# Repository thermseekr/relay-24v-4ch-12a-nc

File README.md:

# eumesmo-rl-4ch12a-nc

Relay board with 4x 24 VDC NC relays. This board is designed to be used togheter with [eumesmo-io-24v16ch](https://github.com/thermseekr/eumesmo-io-24v16ch), but can be driven by any 24V control circuit compatible with NPN inputs. It uses Omron 16A relays and is limited to 12A/channel per copper trace capacity.

The board is compatible with the SP7 DIN rail system from Metaltex.

## VERSION HISTORY

V1.2 - 2026/06/13 - Repository renamed from RELAY-24V-4CH-12A-NC to eumesmo-rl-4ch12A-nc to align the design with the eumesmo line of building automation products.

V1.1 - 2026/06/13 - Input terminal blocks replaced from 2.54mm to 3.5mm pitch for easier installation in the field.

V1.0 - Initial release.

## LICENSE

This project is licensed under the [Creative Commons BY-NC 4.0 License](https://creativecommons.org/licenses/by-nc/4.0/).
Commercial use is not permitted without prior written consent. See the [LICENSE.txt](LICENSE.txt) file for details.

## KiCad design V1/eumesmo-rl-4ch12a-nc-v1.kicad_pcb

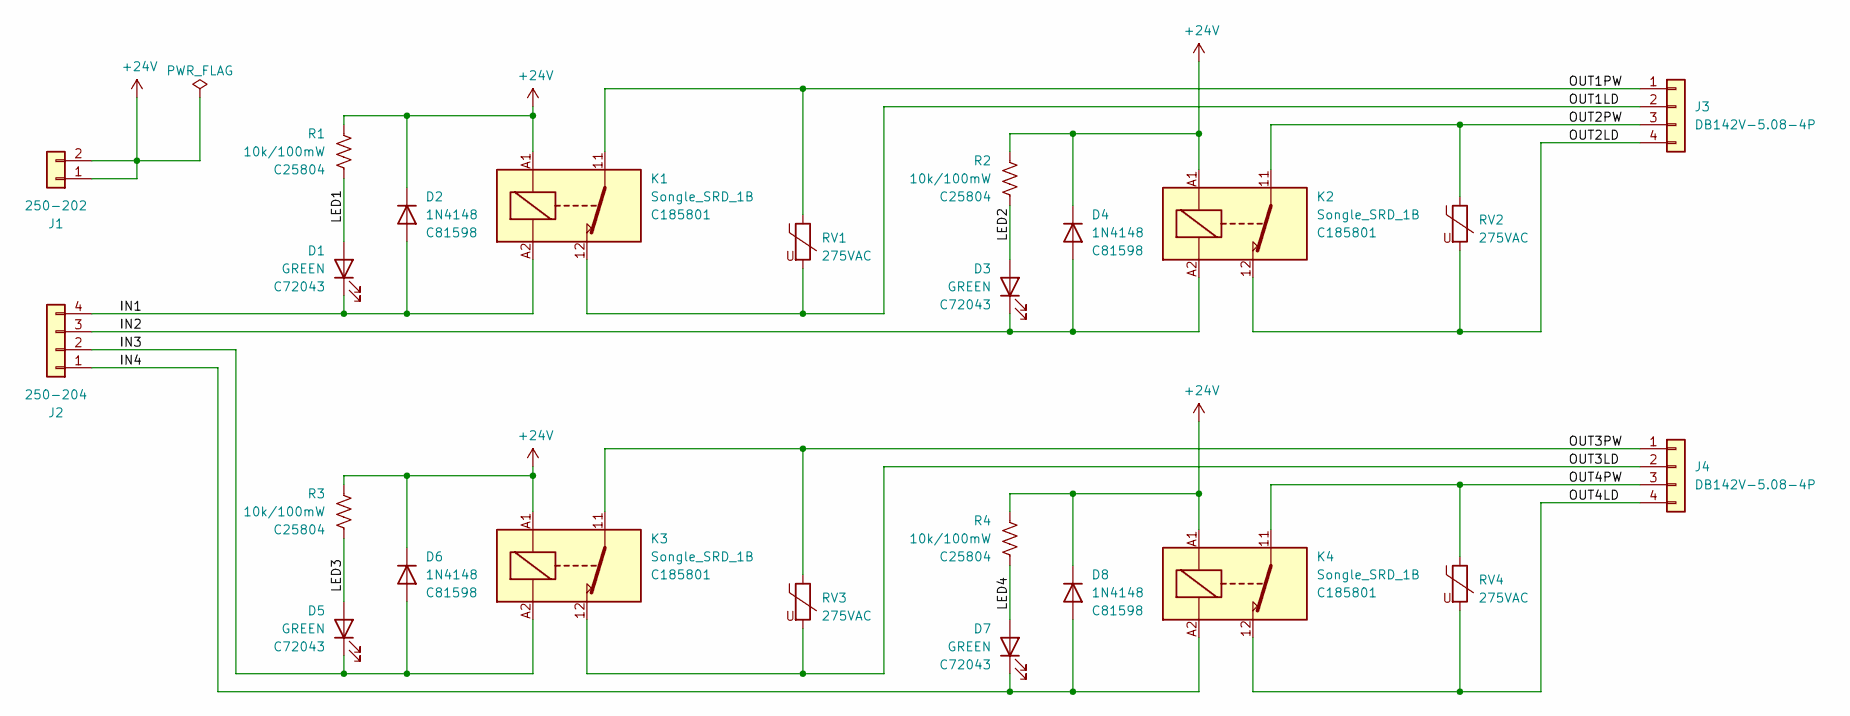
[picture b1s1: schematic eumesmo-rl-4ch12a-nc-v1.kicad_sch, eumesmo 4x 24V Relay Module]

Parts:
D1, D3, D5, D7: GREEN; LED_0603_1608Metric; Mfr PN 19-217/GHC-YR1S2/3T; LCSC Part # C72043
D2, D4, D6, D8: 1N4148; D_SOD-123; Mfr PN 1N4148W; LCSC Part # C81598
J1: 250-202; TerminalBlock_Wago_250-202_1x02_P3.5mm_45Degree; Mfr PN 250-202; JLCPCB BOM 1
J2: 250-204; TerminalBlock_Wago_250-204_1x04_P3.5mm_45Degree; Mfr PN 250-204; JLCPCB BOM 1
J3, J4: DB142V-5.08-4P; TerminalBlock_Dibo_DB142V-5.08-4P_1x04_P5.08mm_Vertical; Mfr PN DB142V-5.08-4P-GN; JLCPCB BOM 1
K1, K2, K3, K4: Songle_SRD_1B; Relay_SPST_Songle_SRD_FormB; Mfr PN SRD-24VDC-SL-B; JLCPCB BOM 1
R1, R2, R3, R4: 10k/100mW; R_0603_1608Metric; Mfr PN 0603WAF1002T5E; LCSC Part # C25804
RV1, RV2, RV3, RV4: 275VAC; RV_Disc_D9.50mm_W3.6mm_P5.08mm; Mfr PN RM07D431KC1IE100; JLCPCB BOM 1

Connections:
+24V: D2.1 (K), D4.1 (K), D6.1 (K), D8.1 (K), J1.1, J1.2, K1.A1, K2.A1, K3.A1, K4.A1, R1.1, R2.1, R3.1, R4.1
/IN1: D1.1 (K), D2.2 (A), J2.4, K1.A2
/IN2: D3.1 (K), D4.2 (A), J2.3, K2.A2
/IN3: D5.1 (K), D6.2 (A), J2.2, K3.A2
/IN4: D7.1 (K), D8.2 (A), J2.1, K4.A2
/LED1: D1.2 (A), R1.2
/LED2: D3.2 (A), R2.2
/LED3: D5.2 (A), R3.2
/LED4: D7.2 (A), R4.2
/OUT1LD: J3.2, K1.12, RV1.2
/OUT1PW: J3.1, K1.11, RV1.1
/OUT2LD: J3.4, K2.12, RV2.2
/OUT2PW: J3.3, K2.11, RV2.1
/OUT3LD: J4.2, K3.12, RV3.2
/OUT3PW: J4.1, K3.11, RV3.1
/OUT4LD: J4.4, K4.12, RV4.2
/OUT4PW: J4.3, K4.11, RV4.1

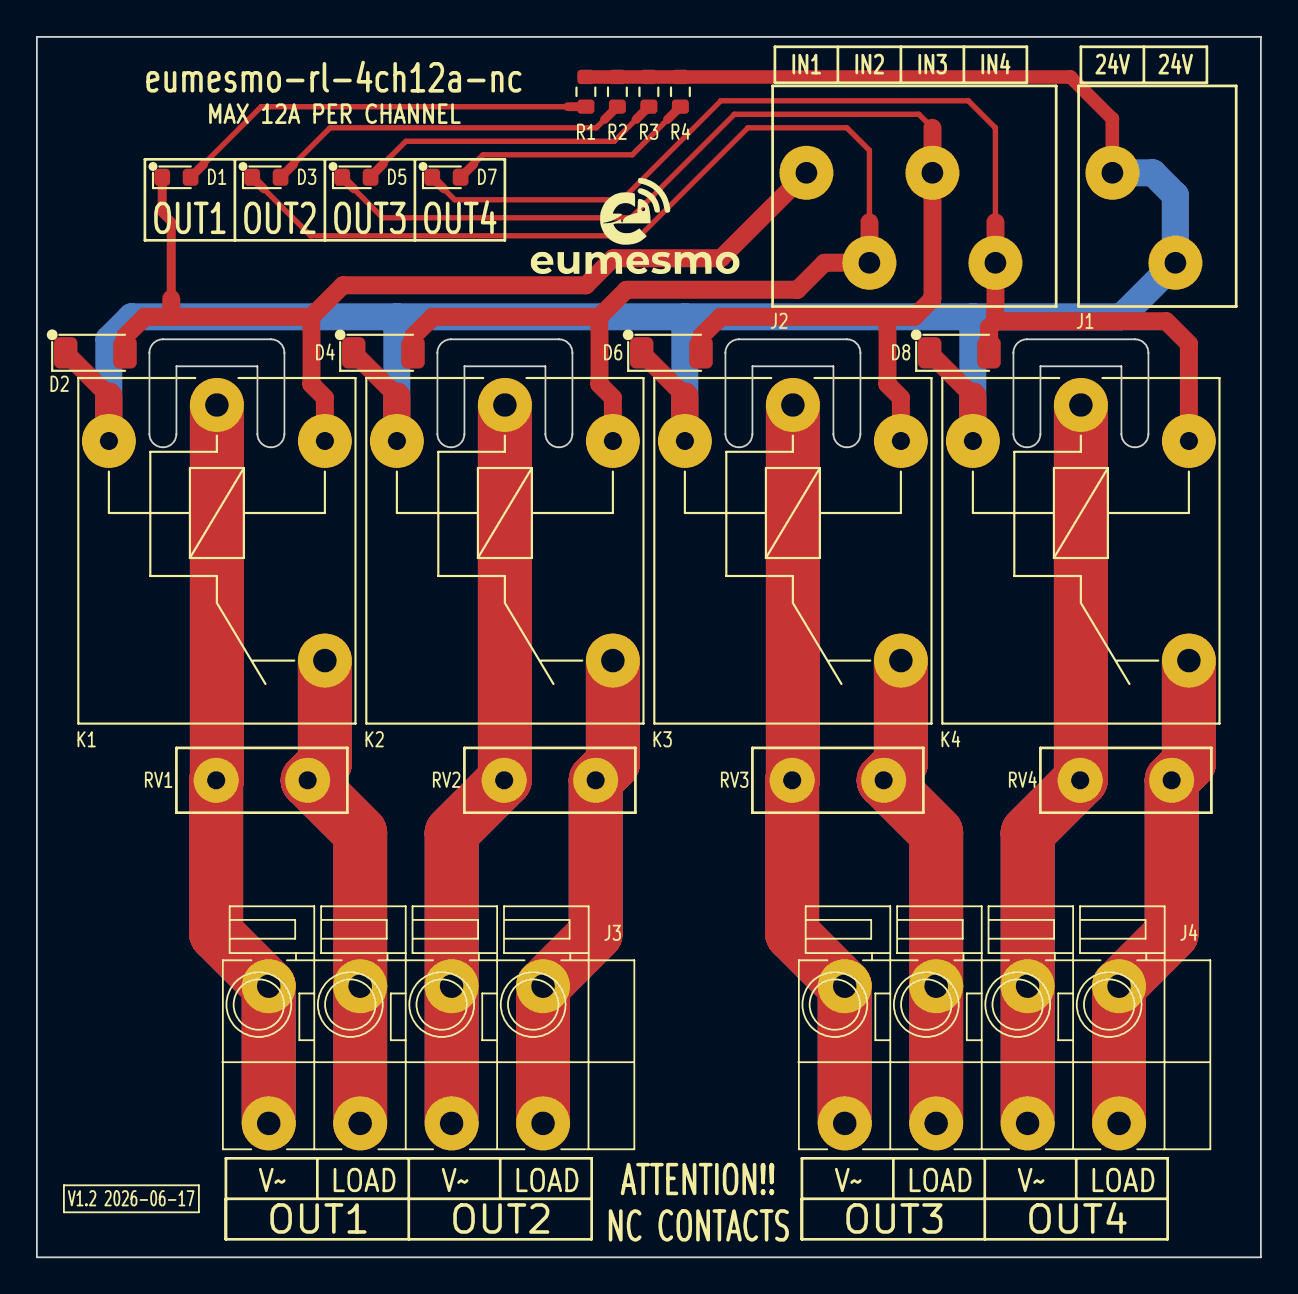
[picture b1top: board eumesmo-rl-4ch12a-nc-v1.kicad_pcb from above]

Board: 2 copper layers, 68.0 x 67.8 mm, 24 parts (0 on the bottom side), 17 nets.

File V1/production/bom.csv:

Designator,Footprint,Quantity,Value,LCSC Part #
"D1, D3, D5, D7",0603,4,GREEN,C72043
"D2, D4, D6, D8",D_SOD-123,4,1N4148,C81598
J1,TerminalBlock_Wago_250-202_1x02_P3.5mm_45Degree,1,250-202,C2765061
J2,TerminalBlock_Wago_250-204_1x04_P3.5mm_45Degree,1,250-204,C2765063
"J3, J4",TerminalBlock_Dibo_DB142V-5.08-4P_1x04_P5.08mm_Vertical,2,DB142V-5.08-4P,C2898701
"K1, K2, K3, K4",Relay_SPST_Songle_SRD_FormB,4,Songle_SRD_1B,C185801
"R1, R2, R3, R4",0603,4,10k/100mW,C25804
"RV1, RV2, RV3, RV4",RV_Disc_D9.50mm_W3.6mm_P5.08mm,4,275VAC,C2761646

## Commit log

2025-05-11 Creating layout
2025-06-22 Updated connectors
2025-06-30 Added license
2025-12-13 Review before fabrication
2026-06-12 Replaced input terminal blocks for 3.5mm pitch.
2026-06-13 Small adjustments to silkscreen
2026-06-13 Moved old releases to oldreleases folder
2026-06-13 Renaming
2026-06-13 Renamed all files to the eumesmo branding
2026-06-13 Adjusted PCB version number.
2026-06-13 Renamed all files to eumesmo branding
2026-06-13 Adjusted version numbers
2026-06-17 Release V1.2.0
